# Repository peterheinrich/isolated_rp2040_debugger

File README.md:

# STATUS: First Prototype in Production
This design is currently untested ...

# Isolated RP2040 Debug Probe

An electrically isolated CMSIS-DAP debug probe based on the Raspberry Pi Debug Probe design, with full USB galvanic isolation for improved safety and robustness when debugging embedded hardware.

This project recreates the Raspberry Pi Debug Probe hardware from the published schematic and adds:

- USB full-speed isolation
- ESD protection on both USB and target ports
- Isolated DC/DC power for the target side
- Improved protection against ground loops and high-energy faults

---

## ⚠️ Important Disclaimer

This is an independent, community-made hardware design.

This project is not affiliated with, endorsed by, or supported by Raspberry Pi Ltd.
“Raspberry Pi” is a trademark of Raspberry Pi Ltd.

The original debug probe design and firmware are created by Raspberry Pi.
This repository only provides a compatible hardware implementation based on their publicly released schematic.

Original documentation:
https://www.raspberrypi.com/documentation/microcontrollers/debug-probe.html

---

## Why an Isolated Debug Probe?

Standard USB debug probes share ground between:

- your PC
- the probe
- the target device

This is usually fine — until it isn't.

Real-world embedded targets often include:
- switching power supplies
- motor drivers
- high-current loads
- long cable harnesses
- industrial equipment

Connecting a non-isolated probe can cause:

- ground loops
- USB disconnects
- corrupted SWD communication
- damage to the target
- damage to your laptop USB port

This design introduces galvanic isolation between the USB host and the target interface (SWD/UART), protecting both sides.

---

## Features

- RP2040-based CMSIS-DAP probe
- SWD debugging (OpenOCD, ... compatible)
- USB CDC UART bridge
- Full USB isolation
- Isolated target power domain
- Drop-in compatible with existing Raspberry Pi Debug Probe software

---

## Hardware Overview

The probe consists of two electrically separated domains:

### Host Side
- USB connector
- USB interface isolator

### Target Side (Isolated)
- RP2040 microcontroller
- SWD interface (SWCLK, SWDIO)
- UART (TX/RX)
- Assumes fixed 3.3V target voltage
- Can power the target (up to 50mA) if desired
- Powered through isolated DC/DC converter

Isolation is implemented using:
- USB isolator IC
- isolated DC/DC converter

No electrical ground connection exists between the PC and the target device.

---

## Firmware

The probe runs the official Raspberry Pi Debug Probe firmware for the RP2040.

Flashing instructions:
1. Connect the probe while holding the BOOTSEL button
2. The device appears as a USB mass storage drive
3. Copy the debugprobe.uf2 firmware to the drive

Firmware download:
https://github.com/raspberrypi/debugprobe/releases

---

## Building the Hardware

### Requirements
- 4-layer PCB recommended
- Hot-air or reflow assembly
- 0603 passives
- Fine-pitch soldering capability

Or simply order via JLCPCB

Files provided in this repository:
- Schematic
- PCB layout
- Gerbers
- BOM
- Pick & Place

---

## Known Limitations

- No more tha 50mA of target power may be supplied by the probe
- USB full-speed only (12 Mbps), same as the original debug probe

---

## License

### This repository
Hardware design files in this repository are released under the CERN-OHL-S v2.

### Raspberry Pi materials
Portions of the information (such as pinout descriptions) are derived from Raspberry Pi documentation, which is licensed under Creative Commons.

© Raspberry Pi Ltd.
Used with attribution.

---

## Acknowledgements

This project would not exist without the excellent work by the Raspberry Pi engineers who designed the original Debug Probe and released its schematic and firmware publicly.

If you simply need a normal probe, please consider buying the official product — it directly supports Raspberry Pi and their open hardware efforts.

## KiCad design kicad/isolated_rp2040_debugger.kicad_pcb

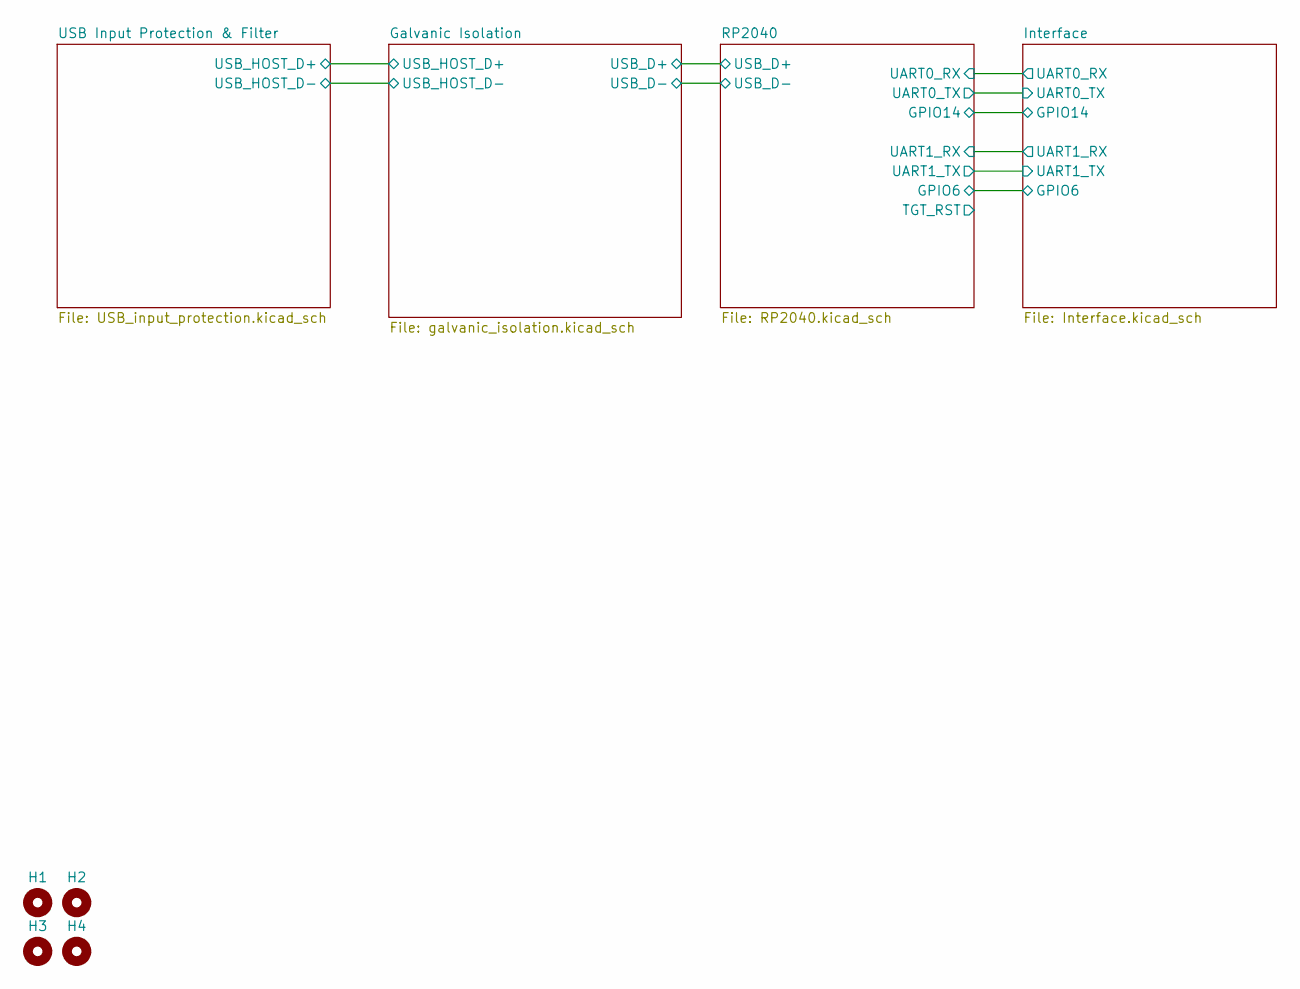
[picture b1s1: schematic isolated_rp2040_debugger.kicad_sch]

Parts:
H1, H2, H3, H4: MountingHole; MountingHole_3.2mm_M3

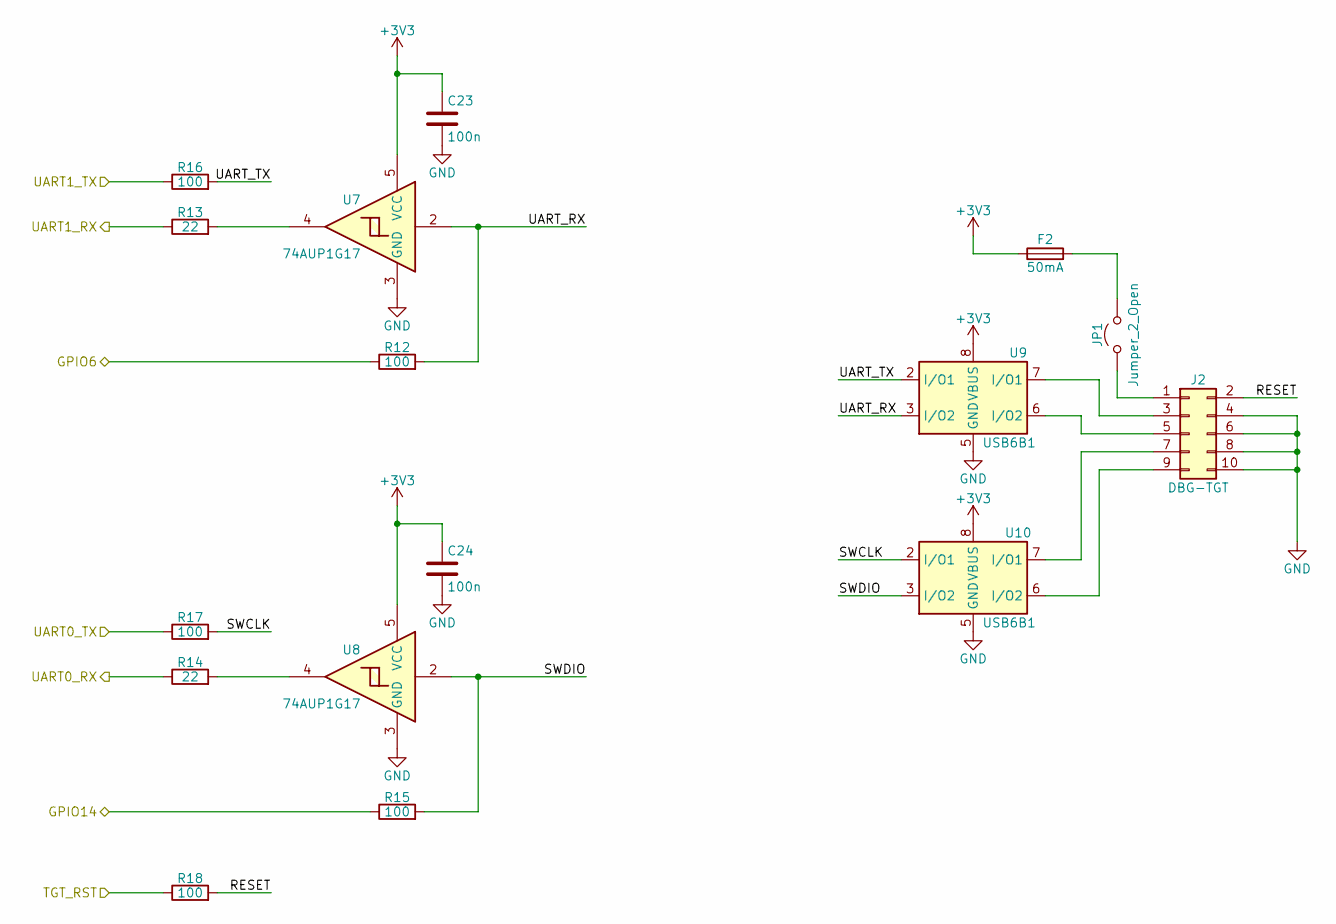
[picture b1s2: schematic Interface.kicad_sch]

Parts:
C23, C24: 100n; C_0603_1608Metric; MPN_LCSC CC0603KRX7R9BB104; LCSC C14663
F2: 50mA; Fuse_1206_3216Metric; MPN_LCSC SMD1206P005TF; LCSC C20797
J2: DBG-TGT; IDC-Header_2x05_P2.54mm_Horizontal; MPN_LCSC 2.54-2*5P弯简牛; LCSC C9140
JP1: Jumper_2_Open; PinHeader_1x02_P2.54mm_Vertical; MPN_LCSC PZ2.54-1*2; LCSC C5360898
R12, R15, R16, R17, R18: 100; R_0603_1608Metric; MPN_LCSC 0603WAF1000T5E; LCSC C22775
R13, R14: 22; R_0603_1608Metric; MPN_LCSC 0603WAJ0220T5E; LCSC C1203
U7, U8: 74AUP1G17; SOT-23-5; MPN_LCSC SN74AUP1G17DBVR; LCSC C183012
U9, U10: USB6B1; SOIC-8_3.9x4.9mm_P1.27mm; MPN_LCSC USB6B1RL; LCSC C10508

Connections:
+3V3: C23.1, C24.1, F2.1, U7.5 (VCC), U8.5 (VCC), U9.1 (VBUS), U9.8 (VBUS), U10.1 (VBUS), U10.8 (VBUS); also elsewhere on the board
/Interface/GPIO6: R12.1; also elsewhere on the board
/Interface/GPIO14: R15.1; also elsewhere on the board
/Interface/RESET: J2.2, R18.2
/Interface/SWCLK: R17.2, U10.2 (I/O1)
/Interface/SWDIO: R15.2, U8.2, U10.3 (I/O2)
/Interface/TGT_RST: R18.1
/Interface/UART0_RX: R14.1; also elsewhere on the board
/Interface/UART0_TX: R17.1; also elsewhere on the board
/Interface/UART1_RX: R13.1; also elsewhere on the board
/Interface/UART1_TX: R16.1; also elsewhere on the board
/Interface/UART_RX: R12.2, U7.2, U9.3 (I/O2)
/Interface/UART_TX: R16.2, U9.2 (I/O1)
GND: C23.2, C24.2, J2.4, J2.6, J2.8, J2.10, U7.3 (GND), U8.3 (GND), U9.4 (GND), U9.5 (GND), U10.4 (GND), U10.5 (GND); also elsewhere on the board
unnamed: J2.1, JP1.1 (A)
unnamed: J2.3, U9.7 (I/O1)
unnamed: J2.5, U9.6 (I/O2)
unnamed: J2.7, U10.7 (I/O1)
unnamed: J2.9, U10.6 (I/O2)
unnamed: F2.2, JP1.2 (B)
unnamed: R13.2, U7.4
unnamed: R14.2, U8.4

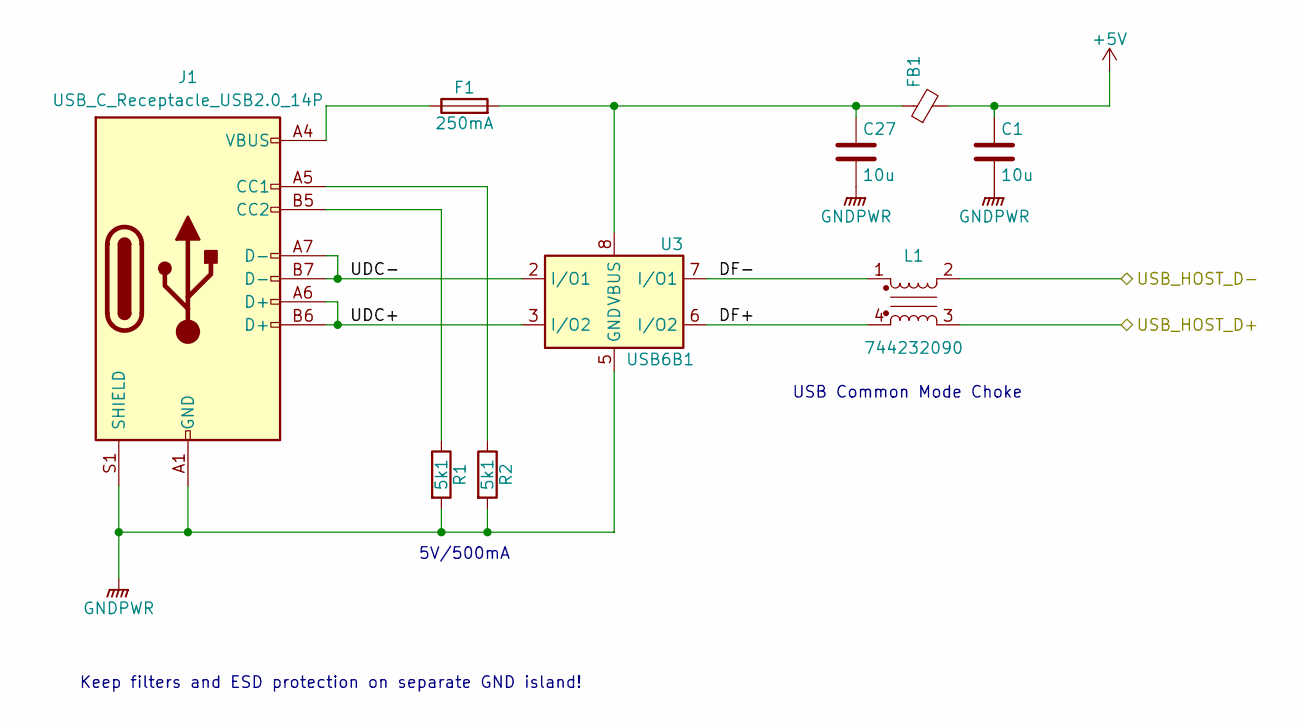
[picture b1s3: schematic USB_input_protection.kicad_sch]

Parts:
C1, C27: 10u; C_0805_2012Metric; MPN_LCSC CL21A106KAYNNNE; LCSC C15850
F1: 250mA; Fuse_1206_3216Metric; MPN_LCSC SMD1206P025TF; LCSC C20798
FB1: L_0805_2012Metric
J1: USB_C_Receptacle_USB2.0_14P; USB_C_Receptacle_HCTL_HC-TYPE-C-16P-01A; MPN_LCSC HC-TYPE-C-16P-01A; LCSC C2894897
L1: 744232090; L_CommonMode_Wurth_WE-CNSW-1206; MPN_LCSC 744232090; LCSC C2649327
R1, R2: 5k1; R_0603_1608Metric; MPN_LCSC 0603WAF5101T5E; LCSC C23186
U3: USB6B1; SOIC-8_3.9x4.9mm_P1.27mm; MPN_LCSC USB6B1RL; LCSC C10508

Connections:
+5V: C1.1, FB1.2; also elsewhere on the board
/Galvanic Isolation/USB_HOST_D+: L1.3; also elsewhere on the board
/Galvanic Isolation/USB_HOST_D-: L1.2; also elsewhere on the board
/USB Input Protection & Filter/DF+: L1.4, U3.6 (I/O2)
/USB Input Protection & Filter/DF-: L1.1, U3.7 (I/O1)
/USB Input Protection & Filter/UDC+: J1.A6 (D+), J1.B6 (D+), U3.3 (I/O2)
/USB Input Protection & Filter/UDC-: J1.A7 (D-), J1.B7 (D-), U3.2 (I/O1)
GNDPWR: C1.2, C27.2, J1.A1 (GND), J1.A12 (GND), J1.B1 (GND), J1.B12 (GND), J1.S1 (SHIELD), R1.2, R2.2, U3.4 (GND), U3.5 (GND); also elsewhere on the board
unnamed: C27.1, F1.2, FB1.1, U3.1 (VBUS), U3.8 (VBUS)
unnamed: F1.1, J1.A4 (VBUS), J1.A9 (VBUS), J1.B4 (VBUS), J1.B9 (VBUS)
unnamed: J1.A5 (CC1), R2.1
unnamed: J1.B5 (CC2), R1.1

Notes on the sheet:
Keep filters and ESD protection on separate GND island!
5V/500mA
USB Common Mode Choke

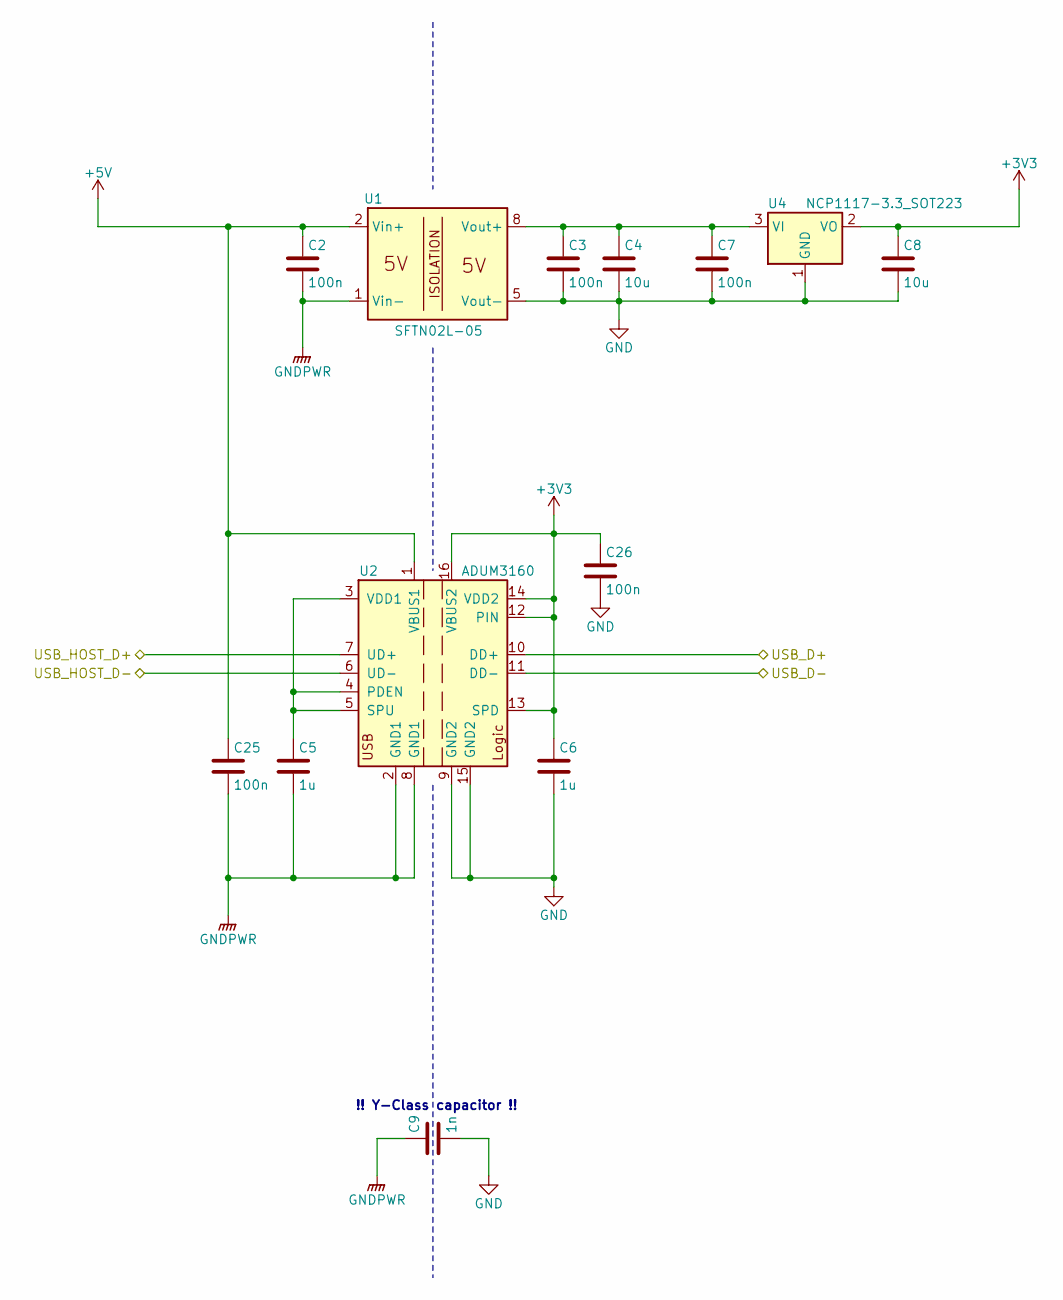
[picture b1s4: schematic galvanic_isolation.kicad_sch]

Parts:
C2, C3, C7, C25, C26: 100n; C_0603_1608Metric; MPN_LCSC CC0603KRX7R9BB104; LCSC C14663
C4, C8: 10u; C_0805_2012Metric; MPN_LCSC CL21A106KAYNNNE; LCSC C15850
C5, C6: 1u; C_0603_1608Metric; MPN_LCSC CL10A105KB8NNNC; LCSC C15849
C9: 1n; C_Disc_D10.0mm_W2.5mm_P5.00mm; MPN_LCSC VY1102M35Y5UQ63V0; LCSC C499502
U1: SMD_DCDC; MPN_LCSC 13DS1-05S05NNL; LCSC C115958
U2: ADUM3160; SOIC-16W_7.5x10.3mm_P1.27mm; MPN_LCSC ADUM3160BRWZ-RL; LCSC C284149
U4: NCP1117-3.3_SOT223; SOT-223-3_TabPin2; MPN_LCSC AMS1117-3.3; LCSC C6186

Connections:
+3V3: C6.1, C8.1, C26.1, U2.12 (PIN), U2.13 (SPD), U2.14 (VDD2), U2.16 (VBUS2), U4.2 (VO); also elsewhere on the board
+5V: C2.1, C25.1, U1.2 (Vin+), U2.1 (VBUS1); also elsewhere on the board
/Galvanic Isolation/USB_D+: U2.10 (DD+); also elsewhere on the board
/Galvanic Isolation/USB_D-: U2.11 (DD-); also elsewhere on the board
/Galvanic Isolation/USB_HOST_D+: U2.7 (UD+); also elsewhere on the board
/Galvanic Isolation/USB_HOST_D-: U2.6 (UD-); also elsewhere on the board
GND: C3.2, C4.2, C6.2, C7.2, C8.2, C9.2, C26.2, U1.5 (Vout-), U2.9 (GND2), U2.15 (GND2), U4.1 (GND); also elsewhere on the board
GNDPWR: C2.2, C5.2, C9.1, C25.2, U1.1 (Vin-), U2.2 (GND1), U2.8 (GND1); also elsewhere on the board
unnamed: C3.1, C4.1, C7.1, U1.8 (Vout+), U4.3 (VI)
unnamed: C5.1, U2.3 (VDD1), U2.4 (PDEN), U2.5 (SPU)

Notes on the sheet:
!! Y-Class capacitor !!

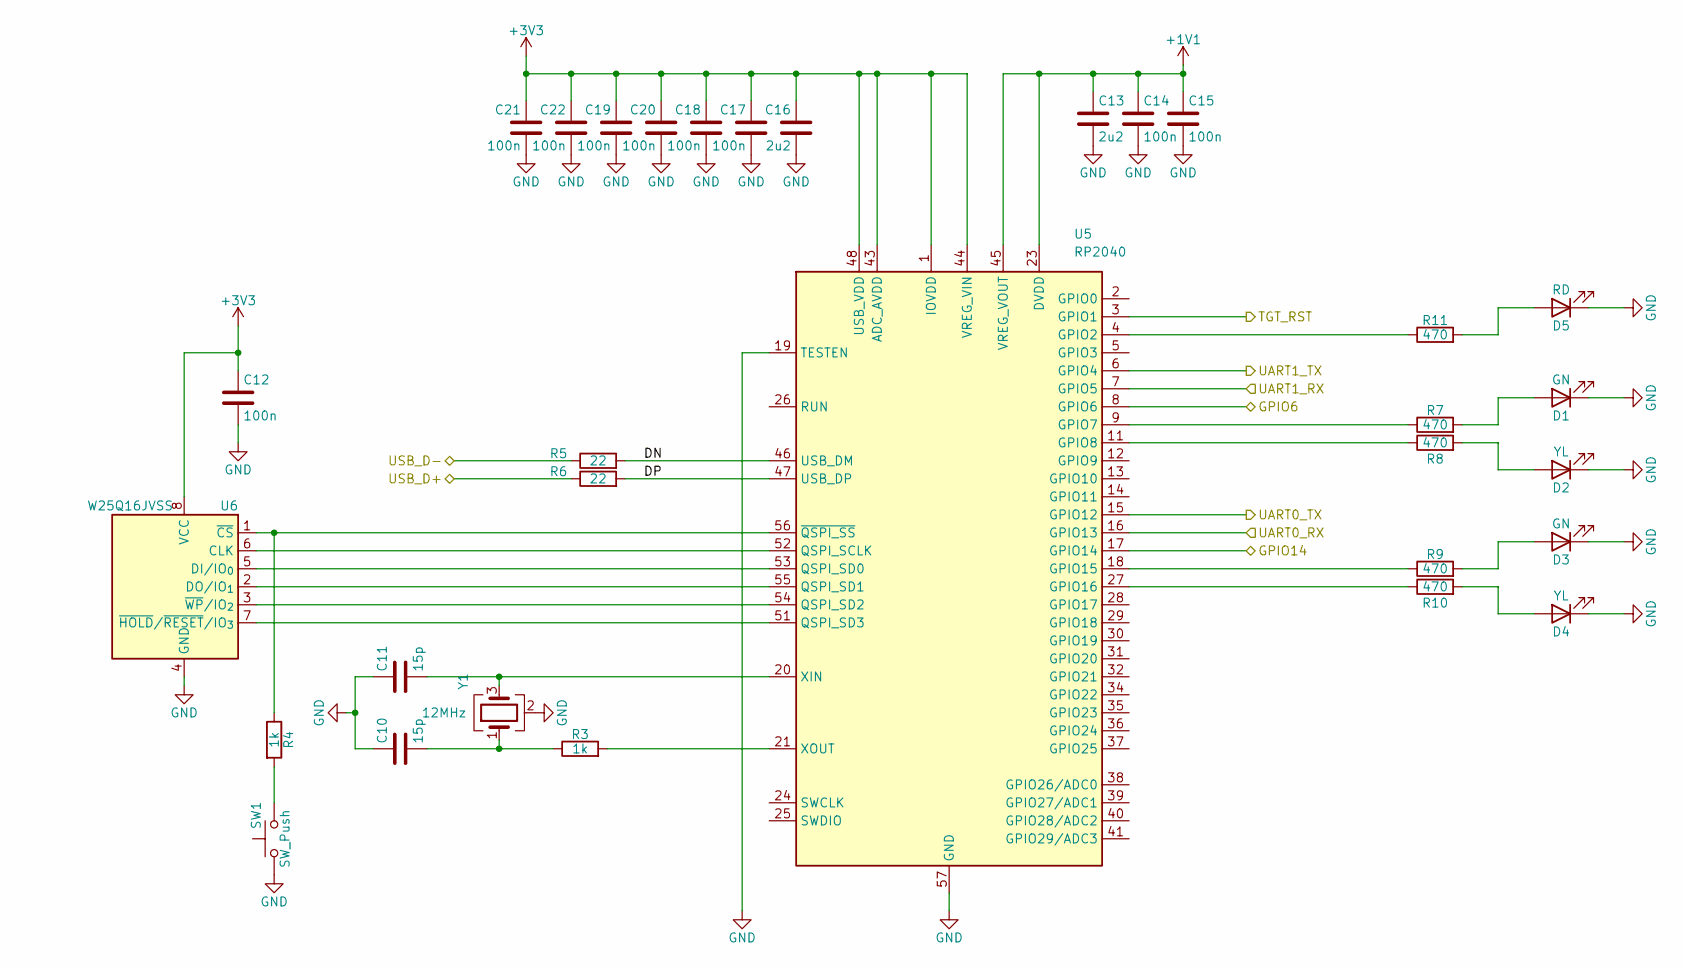
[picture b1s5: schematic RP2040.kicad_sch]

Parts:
C10, C11: 15p; C_0603_1608Metric; MPN_LCSC CL10C150JB8NNNC; LCSC C1644
C12, C14, C15, C17, C18, C19, C20, C21, C22: 100n; C_0603_1608Metric; MPN_LCSC CC0603KRX7R9BB104; LCSC C14663
C13, C16: 2u2; C_0805_2012Metric; MPN_LCSC CL21A225KBQNNNE; LCSC C377773
D1, D3: GN; LED_0805_2012Metric; MPN_LCSC KT-0805G; LCSC C2297
D2, D4: YL; LED_0805_2012Metric; MPN_LCSC KT-0805Y; LCSC C2296
D5: RD; LED_0805_2012Metric; MPN_LCSC NCD0805R1; LCSC C84256
R3, R4: 1k; R_0603_1608Metric; MPN_LCSC 0603WAF1001T5E; LCSC C21190
R5, R6: 22; R_0603_1608Metric; MPN_LCSC 0603WAJ0220T5E; LCSC C1203
R7, R8, R9, R10, R11: 470; R_0603_1608Metric; MPN_LCSC 0603WAF4700T5E; LCSC C23179
SW1: SW_Push; SW_SPST_TS-1088-xR020; MPN_LCSC TS-1088-AR02016; LCSC C720477
U5: RP2040; QFN-56-1EP_7x7mm_P0.4mm_EP3.2x3.2mm; MPN_LCSC RP2040; LCSC C2040
U6: W25Q16JVSS; SOIC-8_5.3x5.3mm_P1.27mm; MPN_LCSC W25Q16JVSSIQ; LCSC C82317
Y1: 12MHz; Crystal_SMD_Abracon_ABM8AIG-4Pin_3.2x2.5mm; MPN_LCSC X322512MSB4SI; LCSC C9002

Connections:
+1V1: C13.1, C14.1, C15.1, U5.23 (DVDD), U5.45 (VREG_VOUT), U5.50 (DVDD)
+3V3: C12.1, C16.1, C17.1, C18.1, C19.1, C20.1, C21.1, C22.1, U5.1 (IOVDD), U5.10 (IOVDD), U5.22 (IOVDD), U5.33 (IOVDD), U5.42 (IOVDD), U5.43 (ADC_AVDD), U5.44 (VREG_VIN), U5.48 (USB_VDD), U5.49 (IOVDD), U6.8 (VCC); also elsewhere on the board
/Galvanic Isolation/USB_D+: R6.1; also elsewhere on the board
/Galvanic Isolation/USB_D-: R5.1; also elsewhere on the board
/Interface/GPIO6: U5.8 (GPIO6); also elsewhere on the board
/Interface/GPIO14: U5.17 (GPIO14); also elsewhere on the board
/Interface/UART0_RX: U5.16 (GPIO13); also elsewhere on the board
/Interface/UART0_TX: U5.15 (GPIO12); also elsewhere on the board
/Interface/UART1_RX: U5.7 (GPIO5); also elsewhere on the board
/Interface/UART1_TX: U5.6 (GPIO4); also elsewhere on the board
/RP2040/DN: R5.2, U5.46 (USB_DM)
/RP2040/DP: R6.2, U5.47 (USB_DP)
/RP2040/TGT_RST: U5.3 (GPIO1)
GND: C10.1, C11.1, C12.2, C13.2, C14.2, C15.2, C16.2, C17.2, C18.2, C19.2, C20.2, C21.2, C22.2, D1.1 (K), D2.1 (K), D3.1 (K), D4.1 (K), D5.1 (K), SW1.1, U5.19 (TESTEN), U5.57 (GND), U6.4 (GND), Y1.2 (G), Y1.4 (G); also elsewhere on the board
unnamed: C10.2, R3.1, Y1.1
unnamed: D1.2 (A), R7.2
unnamed: D2.2 (A), R8.2
unnamed: D3.2 (A), R9.2
unnamed: D4.2 (A), R10.2
unnamed: D5.2 (A), R11.2
unnamed: R4.2, SW1.2
unnamed: R11.1, U5.4 (GPIO2)
unnamed: R7.1, U5.9 (GPIO7)
unnamed: R8.1, U5.11 (GPIO8)
unnamed: R9.1, U5.18 (GPIO15)
unnamed: R10.1, U5.27 (GPIO16)
unnamed: U5.52 (QSPI_SCLK), U6.6 (CLK)
unnamed: U5.53 (QSPI_SD0), U6.5 (DI/IO_{0})
unnamed: U5.55 (QSPI_SD1), U6.2 (DO/IO_{1})
unnamed: U5.54 (QSPI_SD2), U6.3 (~WP/IO_{2})
unnamed: U5.51 (QSPI_SD3), U6.7 (~HOLD/~RESET/IO_{3})
unnamed: C11.2, U5.20 (XIN), Y1.3
unnamed: R3.2, U5.21 (XOUT)
unnamed: R4.1, U5.56 (~QSPI_SS), U6.1 (~CS)

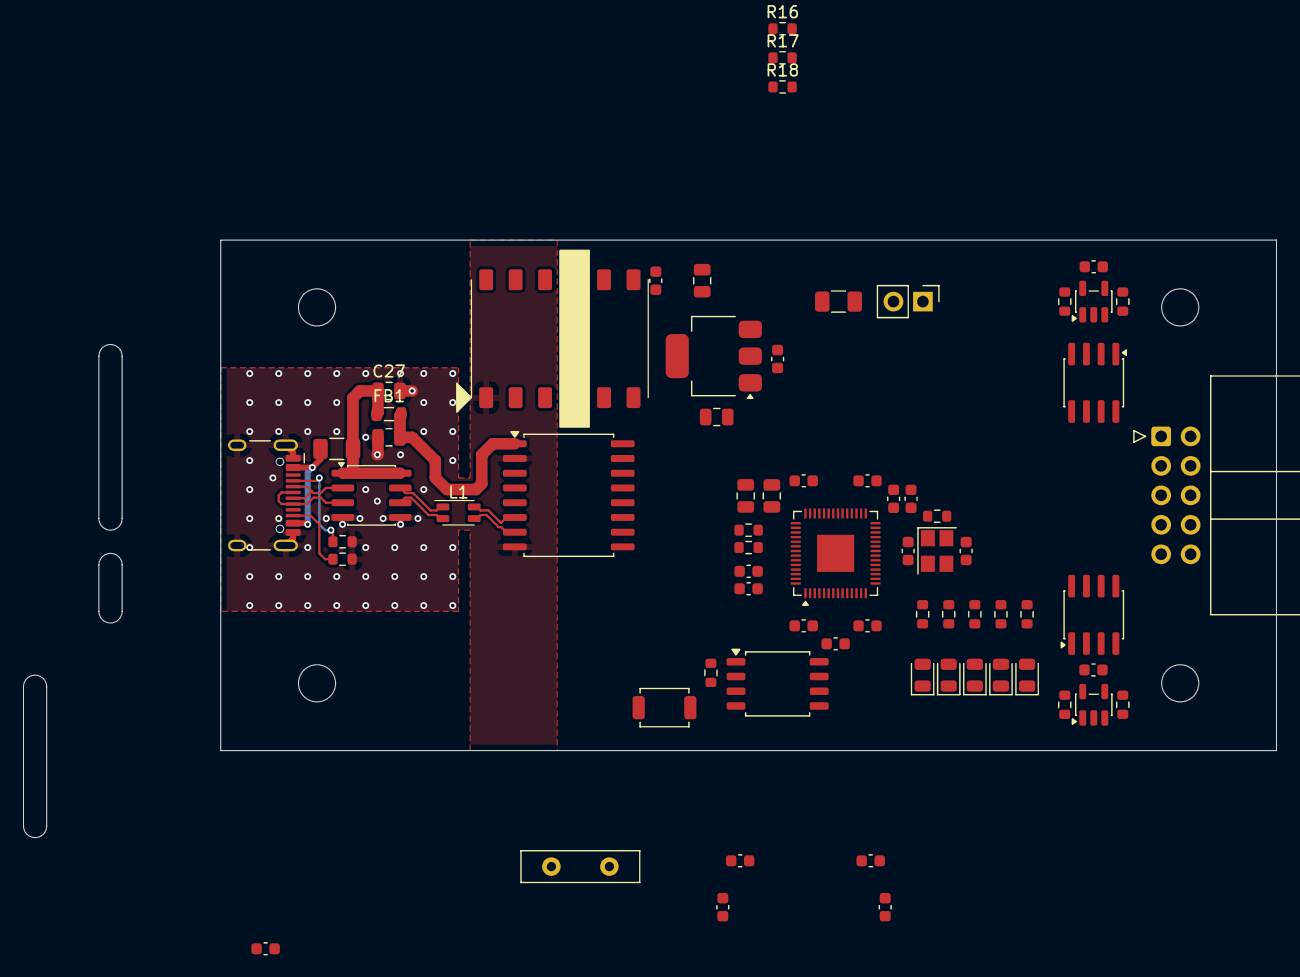
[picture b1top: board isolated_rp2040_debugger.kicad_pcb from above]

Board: 4 copper layers, 91.0 x 44.0 mm, 73 parts (0 on the bottom side), 60 nets.

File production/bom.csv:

Designator,Footprint,Quantity,Value,LCSC Part #
"C1, C4, C8",0805,3,10u,C15850
"C10, C11",0603,2,15p,C1644
"C12, C14, C15, C17, C18, C19, C2, C20, C21, C22, C23, C24, C25, C26, C3, C7",0603,16,100n,C14663
"C13, C16",0805,2,2u2,C377773
"C5, C6",0603,2,1u,C15849
C9,C_Disc_D10.0mm_W2.5mm_P5.00mm,1,1n,C499502
"D1, D3",0805,2,GN,C2297
"D2, D4",0805,2,YL,C2296
D5,0805,1,RD,C84256
F1,1206,1,250mA,C20798
F2,1206,1,50mA,C20797
J1,USB_C_Receptacle_HCTL_HC-TYPE-C-16P-01A,1,USB_C_Receptacle_USB2.0_14P,C2894897
J2,IDC-Header_2x05_P2.54mm_Horizontal,1,DBG-TGT,C9140
JP1,PinHeader_1x02_P2.54mm_Vertical,1,Jumper_2_Open,C5360898
"R1, R2",0603,2,5k1,C23186
"R10, R11, R7, R8, R9",0603,5,470,C23179
"R12, R15",0603,2,100,C22775
"R13, R14",0603,2,22,C1203
"R3, R4, R5, R6",0603,4,1k,C21190
SW1,SW_SPST_TS-1088-xR020,1,SW_Push,C720477
U1,SMD_DCDC,1,~,C115958
"U10, U3, U9",SOIC-8_3.9x4.9mm_P1.27mm,3,USB6B1,C10508
U2,SOIC-16W_7.5x10.3mm_P1.27mm,1,ADUM3160,C284149
U4,SOT-223-3_TabPin2,1,NCP1117-3.3_SOT223,C6186
U5,QFN-56-1EP_7x7mm_P0.4mm_EP3.2x3.2mm,1,RP2040,C2040
U6,SOIC-8_5.3x5.3mm_P1.27mm,1,W25Q16JVSS,C82317
"U7, U8",SOT-23-5,2,74AUP1G17,C183012
Y1,Crystal_SMD_Abracon_ABM8AIG-4Pin_3.2x2.5mm,1,12MHz,C9002

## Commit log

2026-02-15 Rev_A JLCPCB Production
2026-02-15 Writing a proper README.md
2026-02-15 Add status section to README
    Added status update for the prototype.
2026-02-16 Adding production rendering of PCB
2026-02-16 Clarify license statement in README
2026-02-16 Remove negative voltage protection from README
2026-03-08 starting redesign
